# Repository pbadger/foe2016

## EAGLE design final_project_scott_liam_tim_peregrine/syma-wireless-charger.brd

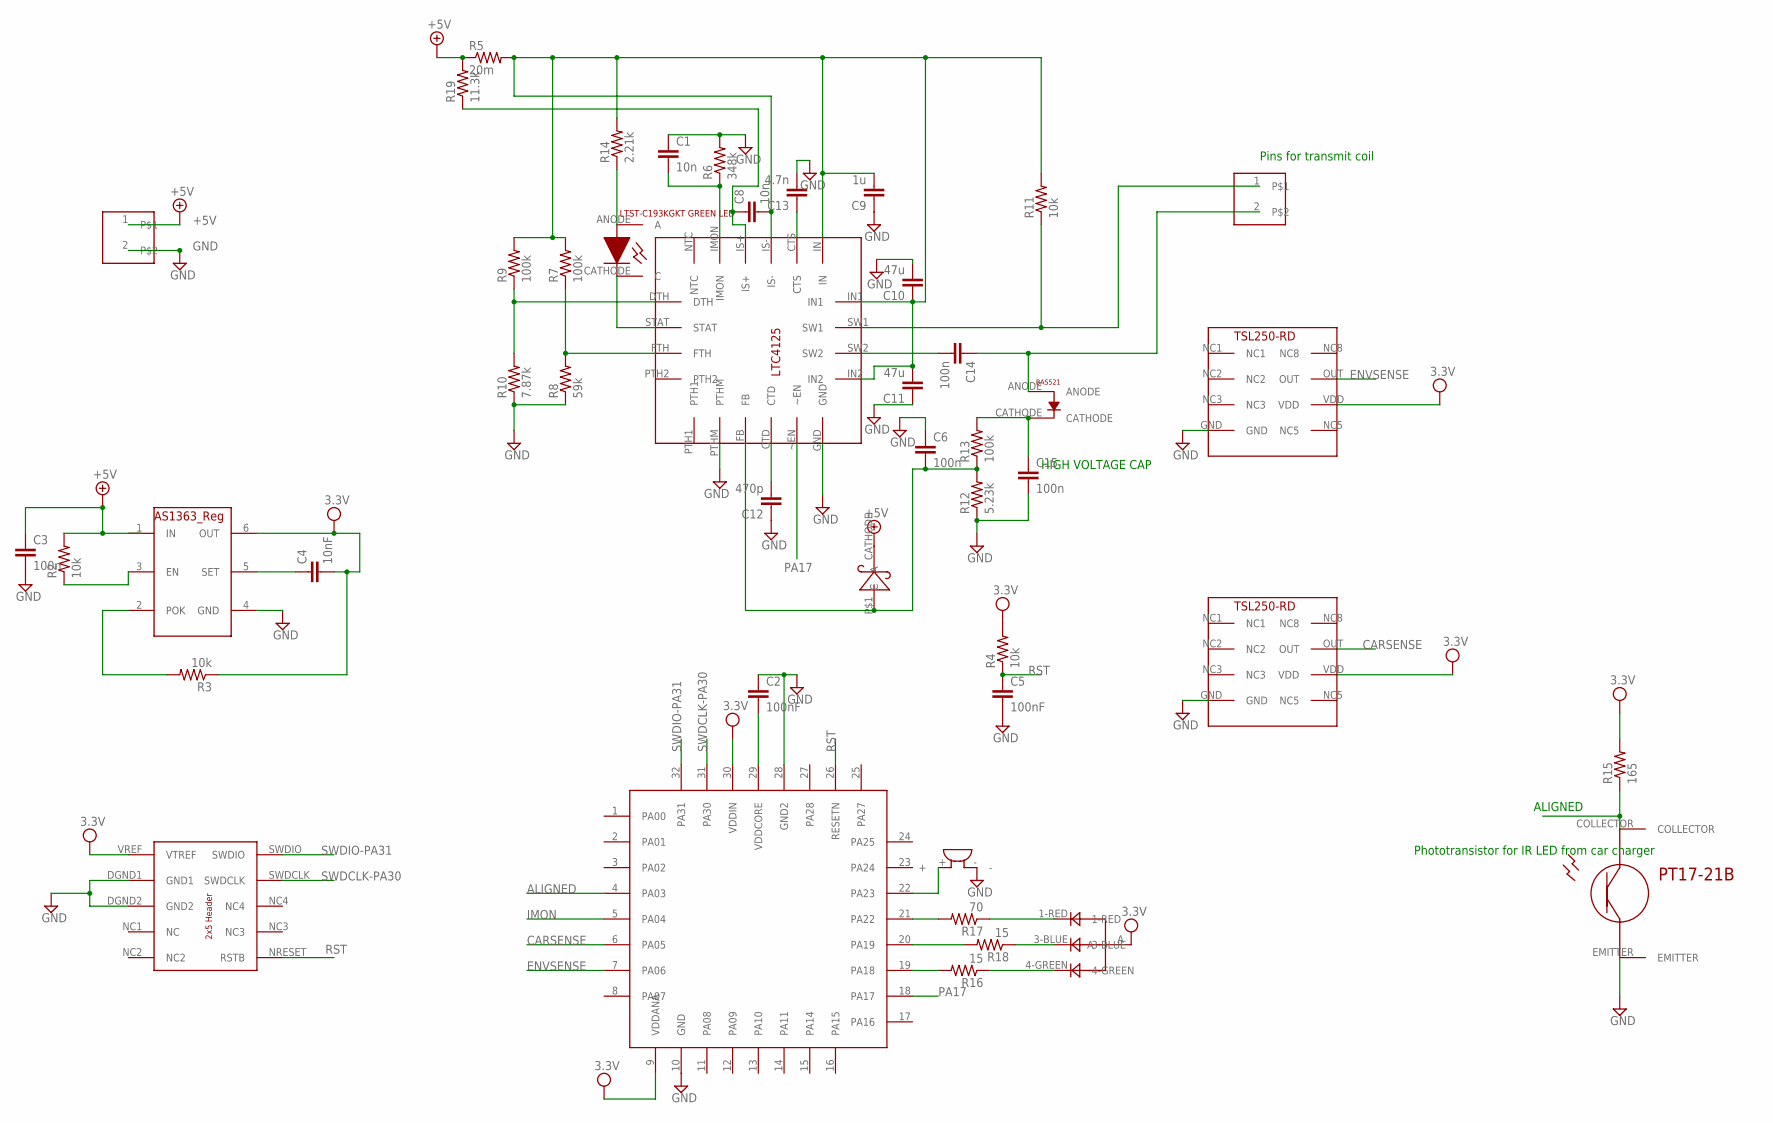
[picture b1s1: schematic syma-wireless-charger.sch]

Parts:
C1, C8: 10n; C0805
C2, C5: 100nF; C0805K
C3: 100n; C0805K
C4: 10nF; C0805K
C6: 100n; C0805
C9: 1u; C0805
C10, C11: 47u; C0805
C12: 470p; C0805
C13: 4.7n; C0805
C14: 100n; C1206
C15: 100n; C0603
DBG1: DEBUGHEAD
R2, R3, R4, R11: 10k; R0805
R5: 20m; R0805
R6: 348k; R0805
R7, R9, R13: 100k; R0805
R8: 59k; R0805
R10: 7.87k; R0805
R12: 5.23k; R0805
R14: 2.21k; R0805
R15: 165; R0805
R16, R18: 15; R0805
R17: 70; R0805
R19: 11.3k; R0805
U1: SAMD21E; TQFP32-08
U2: 3.3V_AS1363; SOT23-6
U$1: LTC4125; LTC1945-QFN
U$2: BAS521; BAS521-V-DIODE
U$3, U$11: 1X02
U$4: RGBLED
U$5: BUZZER
U$6, U$7: TSL250-RD
U$8: SCHTKYDIODE-523; SOD-523
U$9: LTST-C193KGKT_GREEN-LED
U$10: PT17-21B_PHOTOTRANSISTOR

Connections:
+5V: C3.1, R2.2, R5.1, R19.2, U2.1 (IN), U$3.1, U$8.CATHODE (C)
ALIGNED: R15.1, U1.4 (PA03), U$10.COLLECTOR
CARSENSE: U1.6 (PA05), U$6.OUT
ENVSENSE: U1.7 (PA06), U$7.OUT
GND: C1.1, C2.1, C3.2, C5.2, C6.1, C9.1, C10.2, C11.1, C12.1, C13.2, C15.2, DBG1.DGND1 (GND1), DBG1.DGND2 (GND2), R6.2, R8.1, R10.1, R12.1, U1.10 (GND), U1.28 (GND2), U2.4 (GND), U$1.GND, U$1.GND2, U$1.PTHM, U$3.2, U$5.-, U$6.GND, U$7.GND, U$10.EMITTER
IMON: U1.5 (PA04)
unnamed: C2.2, U1.29 (VDDCORE)
unnamed: R3.2, U2.2 (POK)
unnamed: R2.1, U2.3 (EN)
unnamed: R9.1, R10.2, U$1.DTH
unnamed: C4.1, U2.5 (SET)
unnamed: R7.1, R8.2, U$1.FTH
unnamed: R11.1, U$1.SW1, U$11.1
unnamed: C1.2, R6.1, U$1.IMON
unnamed: C6.2, R12.2, R13.1, U$1.FB, U$8.P$1 (A)
unnamed: C15.1, R13.2, U$2.CATHODE
unnamed: R14.1, U$9.ANODE (A)
unnamed: C14.1, U$2.ANODE, U$11.2
unnamed: R17.2, U1.21 (PA22)
unnamed: R18.2, U1.20 (PA19)
unnamed: R16.2, U1.19 (PA18)
unnamed: R16.1, U$4.4-GREEN
unnamed: R18.1, U$4.3-BLUE
unnamed: R17.1, U$4.1-RED
unnamed: U1.22 (PA23), U$5.+
unnamed: C8.2, C9.2, C10.1, C11.2, R5.2, R7.2, R9.2, R11.2, R14.2, U$1.IN, U$1.IN1, U$1.IN2, U$1.IS-
unnamed: C8.1, R19.1, U$1.IS+
unnamed: C14.2, U$1.SW2
unnamed: U$1.STAT, U$9.CATHODE (C)
unnamed: C12.2, U$1.CTD
unnamed: C13.1, U$1.CTS
PA17: U1.18 (PA17), U$1.~EN
RST: C5.1, DBG1.NRESET (RSTB), R4.1, U1.26 (RESETN)
SWDCLK-PA30: DBG1.SWDCLK, U1.31 (PA30)
SWDIO-PA31: DBG1.SWDIO, U1.32 (PA31)

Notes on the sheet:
Phototransistor for IR LED from car charger
Pins for transmit coil
HIGH VOLTAGE CAP
ALIGNED

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
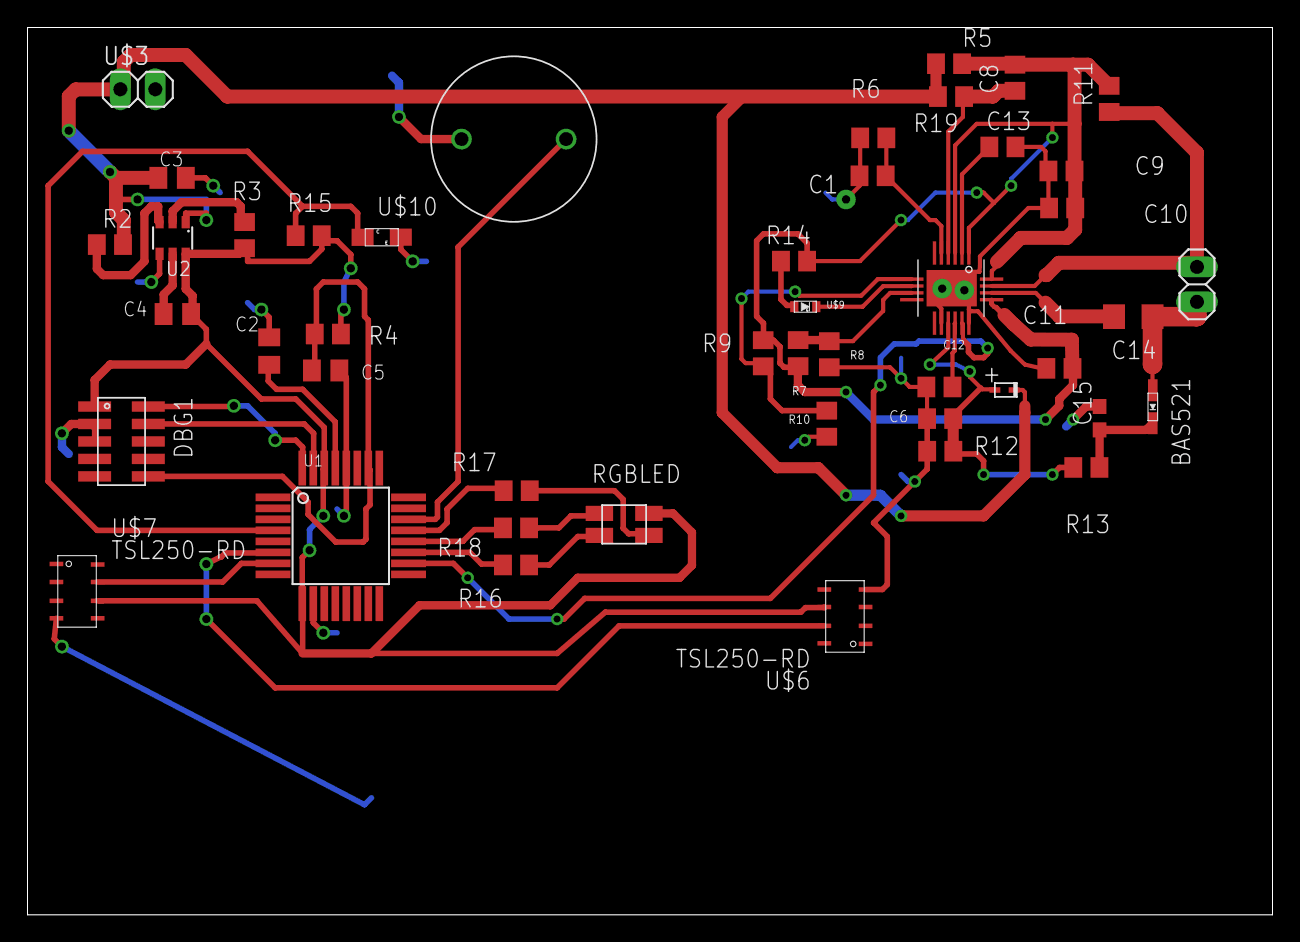
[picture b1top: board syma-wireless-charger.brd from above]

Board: 2 copper layers, 90.5 x 64.5 mm, 46 parts (0 on the bottom side), 35 nets.

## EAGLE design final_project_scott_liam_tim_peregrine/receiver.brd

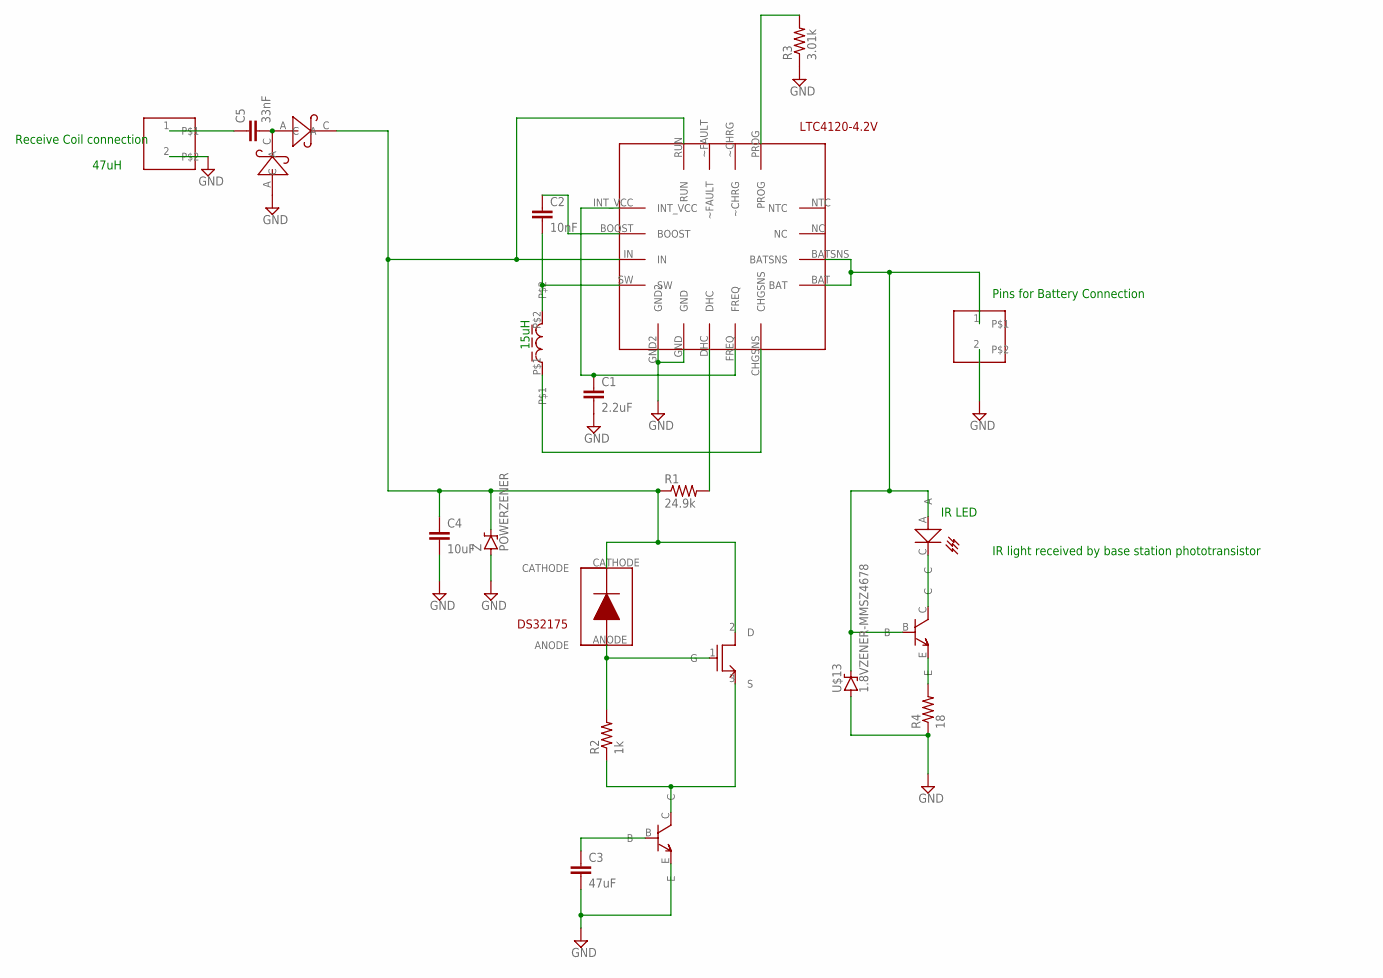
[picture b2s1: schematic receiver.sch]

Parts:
C1: 2.2uF; C0805K
C2: 10nF; C0805K
C3: 47uF; C0805K
C4: 10uF; C0805K
C5: 33nF; C0805K
PS, PS2: SCHTKYPOWER; POWERDI123
R1: 24.9k; R0805
R2: 1k; R0805
R3: 3.01k; R0805
R4: 18; R0805
U$1: LTC4120-4.2V
U$2, U$10: 1X02
U$3: 15UH-INDUCTOR
U$4: BAS521; BAS521-V-DIODE
U$5: M1-RSD140P06; DPAKTO252
U$6, U$14: NPN-MMBT3904; SOT23
U$11: IRLED
U$13: 1.8VZENER-MMSZ4678; SOD-123
Z: POWERZENER; POWERDI123

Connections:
GND: C1.2, C3.2, C4.2, PS2.A, R3.1, R4.1, U$1.GND, U$1.GND2, U$2.2, U$6.E, U$10.2, U$13.A, Z.A
unnamed: C1.1, U$1.FREQ, U$1.INT_VCC
unnamed: U$1.CHGSNS, U$3.P$1
unnamed: C4.1, PS.C, R1.1, U$1.IN, U$1.RUN, U$4.CATHODE, U$5.2 (D), Z.C
unnamed: C2.1, U$1.BOOST
unnamed: C2.2, U$1.SW, U$3.P$2
unnamed: R1.2, U$1.DHC
unnamed: R2.2, U$4.ANODE, U$5.1 (G)
unnamed: R2.1, U$5.3 (S), U$6.C
unnamed: C5.1, U$2.1
unnamed: C5.2, PS.A, PS2.C
unnamed: C3.1, U$6.B
unnamed: R3.2, U$1.PROG
unnamed: U$1.BAT, U$1.BATSNS, U$10.1, U$11.A, U$13.C, U$14.B
unnamed: R4.2, U$14.E
unnamed: U$11.C, U$14.C

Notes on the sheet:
15uH
Pins for Battery Connection
IR LED
IR light received by base station phototransistor
Receive Coil connection
47uH

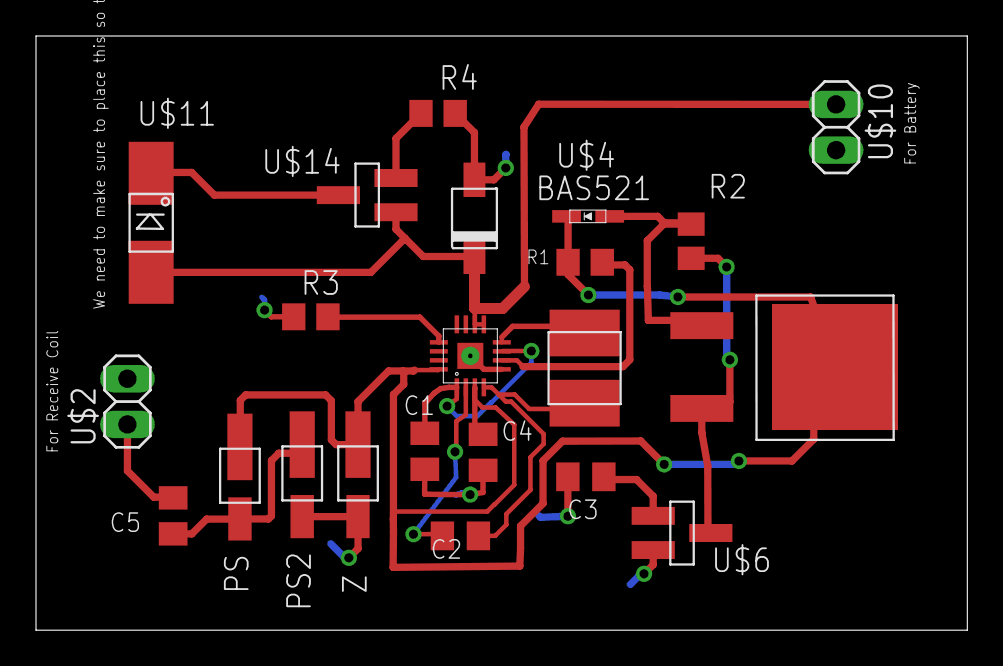
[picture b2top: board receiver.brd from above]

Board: 2 copper layers, 51.7 x 33.0 mm, 22 parts (0 on the bottom side), 16 nets.

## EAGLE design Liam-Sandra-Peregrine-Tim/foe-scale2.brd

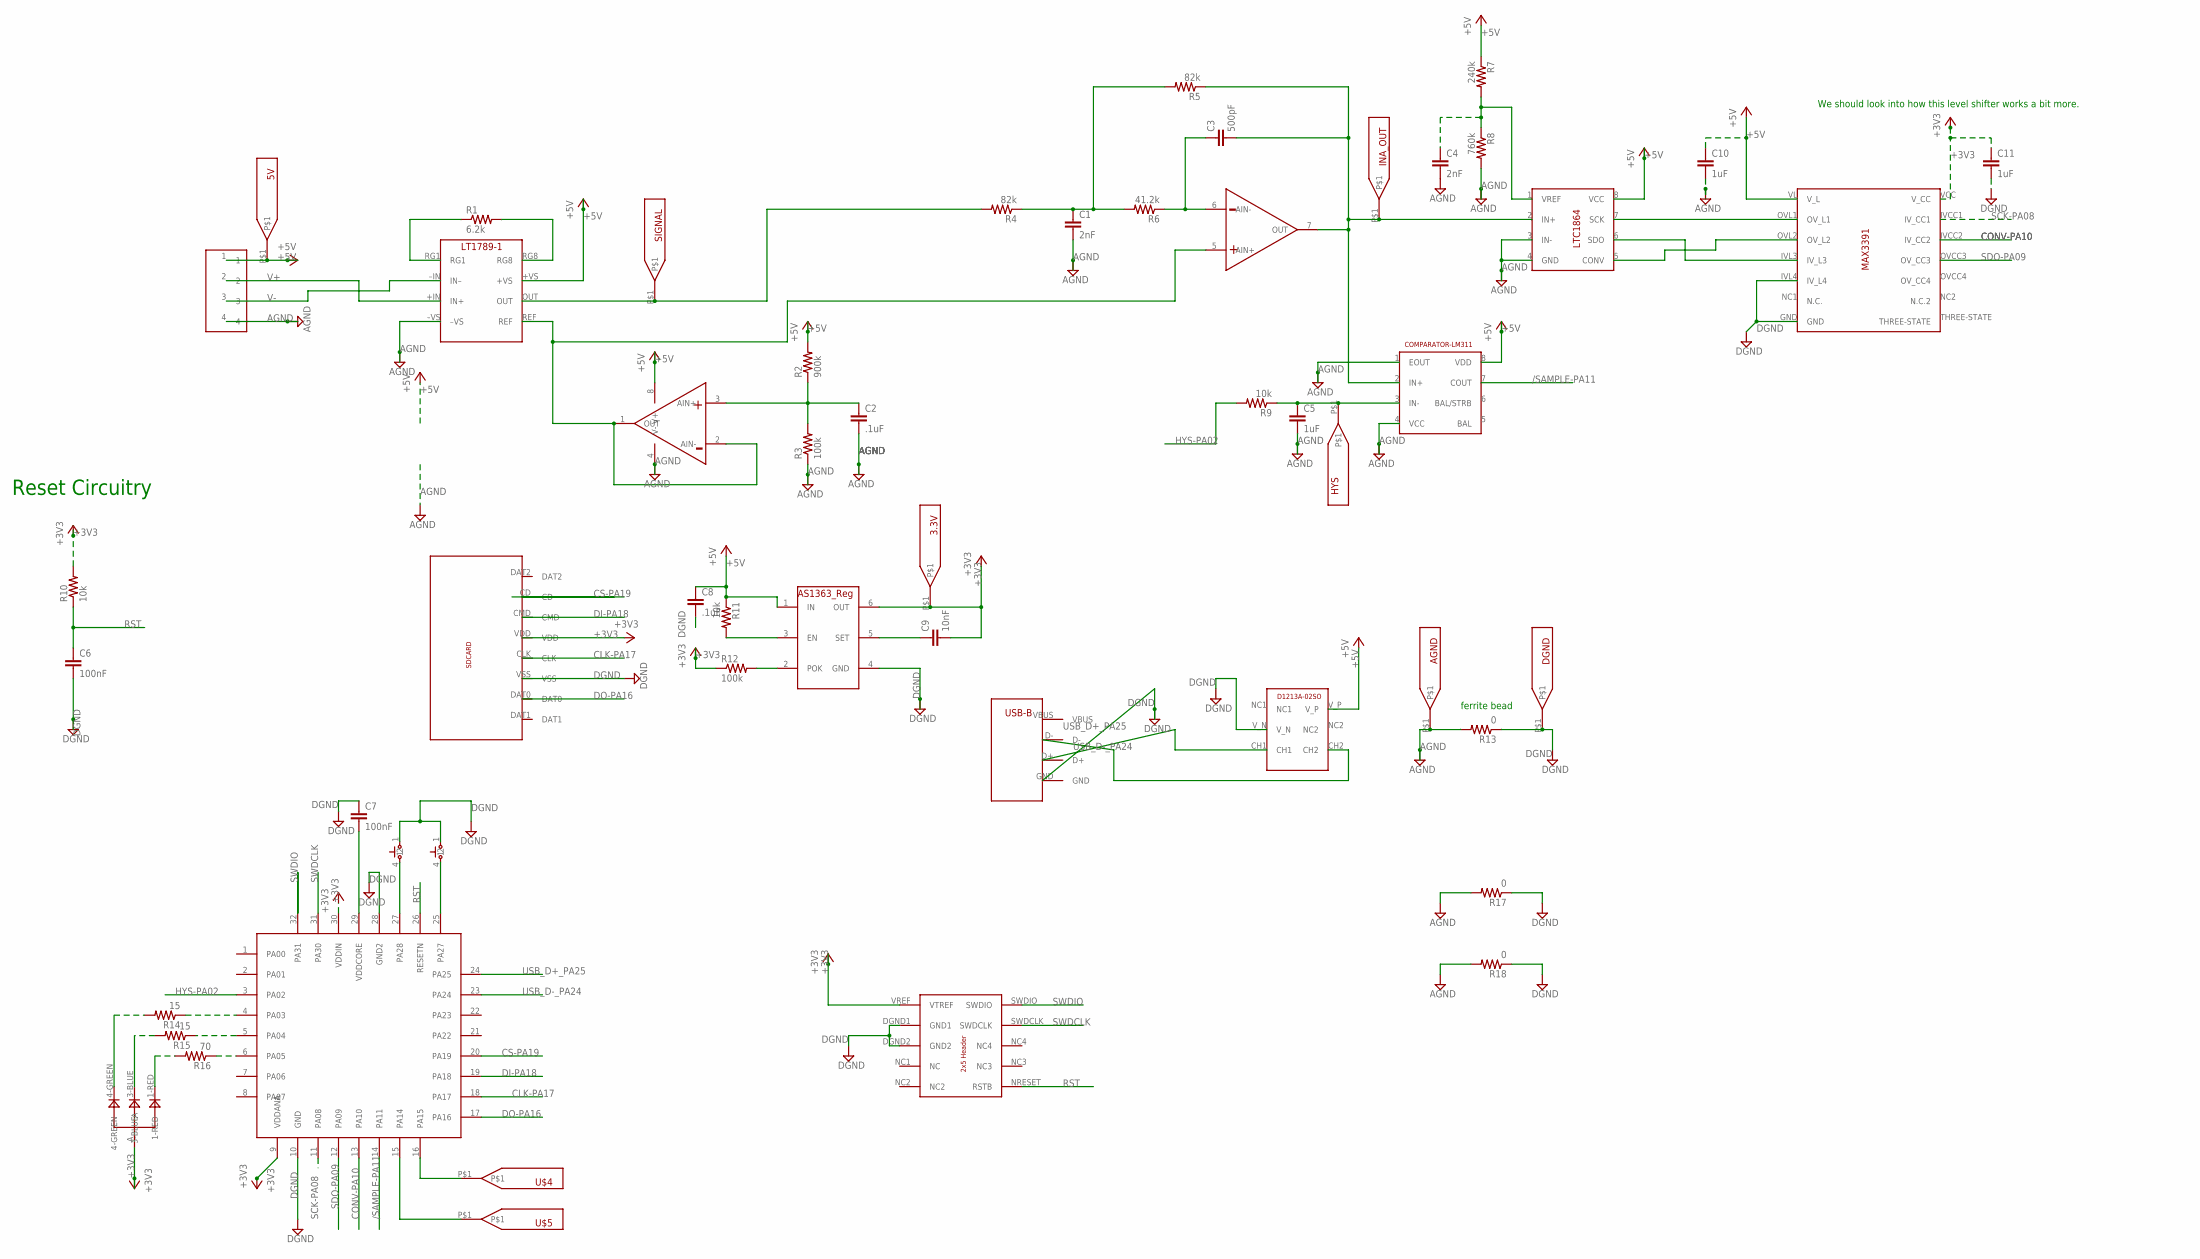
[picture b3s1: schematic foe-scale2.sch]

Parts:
3.3V, 5V: TEST_POINT
AGND: TEST_POINT
AS1363: 3.3V_AS1363; SOT23-6
C1, C4: 2nF; C0805K
C2, C8: .1uF; C0805K
C3: 500pF; C0805K
C5, C10, C11: 1uF; C0805K
C6, C7: 100nF; C0805K
C9: 10nF; C0805K
D1: D1213A-DIODE-ARRAY; SOT26-DIODE-ARRAY
DBG1: DEBUGHEAD
DGND: TEST_POINT
HYS: TEST_POINT
INA_OUT: TEST_POINT
R1: 6.2k; R0805
R2: 900k; R0805
R3, R12: 100k; R0805
R4, R5: 82k; R0805
R6: 41.2k; R0805
R7: 240k; R0805
R8: 760k; R0805
R9, R10, R11: 10k; R0805
R13, R17, R18: 0; R0805
R14, R15: 15; R0805
R16: 70; R0805
SIGNAL: TEST_POINT
U1: LM311; SOIC8
U2: SAMD21E; TQFP32-08
U$1: 1X04
U$2: LT1789-1-INSTR-AMP; S8-LT1789-1
U$3: LMC6482; SOIC8
U$4, U$5: TEST_POINT
U$6: ADC-LTC1864; SOIC8
U$7: LEVEL-SHIFTER; TSSOP-14
U$8: SDCARD_JACK; MICRO_SDCARD
U$10: RGBLED
U$11, U$12: BUTTON_THRU; PUSHBTN
U$13: USB-B

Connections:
+3V3: 3.3V.P$1, AS1363.6 (OUT), C9.2, C11.1, DBG1.VREF (VTREF), R10.2, R12.1, U2.9 (VDDANA), U2.30 (VDDIN), U$7.VCC (V_CC), U$8.VDD, U$10.A
+5V: 5V.P$1, AS1363.1 (IN), C8.1, C10.1, D1.V_P, R2.2, R7.1, R11.1, U1.8 (VDD), U$1.1, U$2.+VS, U$3.8 (V+), U$6.8 (VCC), U$7.VL (V_L)
/SAMPLE-PA11: U1.7 (COUT), U2.14 (PA11)
AGND: AGND.P$1, C1.2, C2.2, C4.2, C5.2, C10.2, R3.1, R8.2, R13.2, R17.2, R18.2, U1.1 (EOUT), U1.4 (VCC), U$1.4, U$2.–VS, U$3.4 (V-), U$6.3 (IN-), U$6.4 (GND)
CLK-PA17: U2.18 (PA17), U$8.CLK
CONV-PA10: U2.13 (PA10), U$7.IVCC2 (IV_CC2)
CS-PA19: U2.20 (PA19), U$8.CD
DBG-2-PA16: U2.16 (PA15), U$4.P$1
DBG-PIN-PA14: U2.15 (PA14), U$5.P$1
DGND: AS1363.4 (GND), C6.2, C7.1, C8.2, C11.2, D1.V_N, DBG1.DGND1 (GND1), DBG1.DGND2 (GND2), DGND.P$1, R13.1, R17.1, R18.1, U2.10 (GND), U2.28 (GND2), U$7.GND, U$7.IVL4 (IV_L4), U$8.VSS, U$11.1, U$12.1, U$13.GND
DI-PA18: U2.19 (PA18), U$8.CMD
DO-PA16: U2.17 (PA16), U$8.DAT0
HYS-PA02: R9.2, U2.3 (PA02)
unnamed: R14.1, U2.4 (PA03)
unnamed: U2.27 (PA28), U$12.4 (2)
unnamed: U2.25 (PA27), U$11.4 (2)
unnamed: R15.1, U2.5 (PA04)
unnamed: R1.1, U$2.RG1
unnamed: R1.2, U$2.RG8
unnamed: R4.2, SIGNAL.P$1, U$2.OUT
unnamed: R16.1, U2.6 (PA05)
unnamed: C2.1, R2.1, R3.2, U$3.3 (AIN+)
unnamed: U$2.REF, U$3.1 (OUT), U$3.2 (AIN-), U$3.5 (AIN+)
unnamed: C1.1, R4.1, R5.2, R6.2
unnamed: C3.2, INA_OUT.P$1, R5.1, U1.2 (IN+), U$3.7 (OUT), U$6.2 (IN+)
unnamed: C3.1, R6.1, U$3.6 (AIN-)
unnamed: C4.1, R7.2, R8.1, U$6.1 (VREF)
unnamed: C5.1, HYS.P$1, R9.1, U1.3 (IN-)
unnamed: U$6.7 (SCK), U$7.OVL1 (OV_L1)
unnamed: U$6.5 (CONV), U$7.OVL2 (OV_L2)
unnamed: U$6.6 (SDO), U$7.IVL3 (IV_L3)
unnamed: C7.2, U2.29 (VDDCORE)
unnamed: R14.2, U$10.4-GREEN
unnamed: R15.2, U$10.3-BLUE
unnamed: R16.2, U$10.1-RED
unnamed: AS1363.3 (EN), R11.2
unnamed: AS1363.5 (SET), C9.1
unnamed: AS1363.2 (POK), R12.2
RST: C6.1, DBG1.NRESET (RSTB), R10.1, U2.26 (RESETN)
SCK-PA08: U2.11 (PA08), U$7.IVCC1 (IV_CC1)
SDO-PA09: U2.12 (PA09), U$7.OVCC3 (OV_CC3)
SWDCLK: DBG1.SWDCLK, U2.31 (PA30)
SWDIO: DBG1.SWDIO, U2.32 (PA31)
USB_D+_PA25: D1.CH1, U2.24 (PA25), U$13.D+
USB_D-_PA24: D1.CH2, U2.23 (PA24), U$13.D-
V+: U$1.2, U$2.+IN (IN+)
V-: U$1.3, U$2.–IN (IN–)

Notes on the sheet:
We should look into how this level shifter works a bit more.
Reset Circuitry
ferrite bead

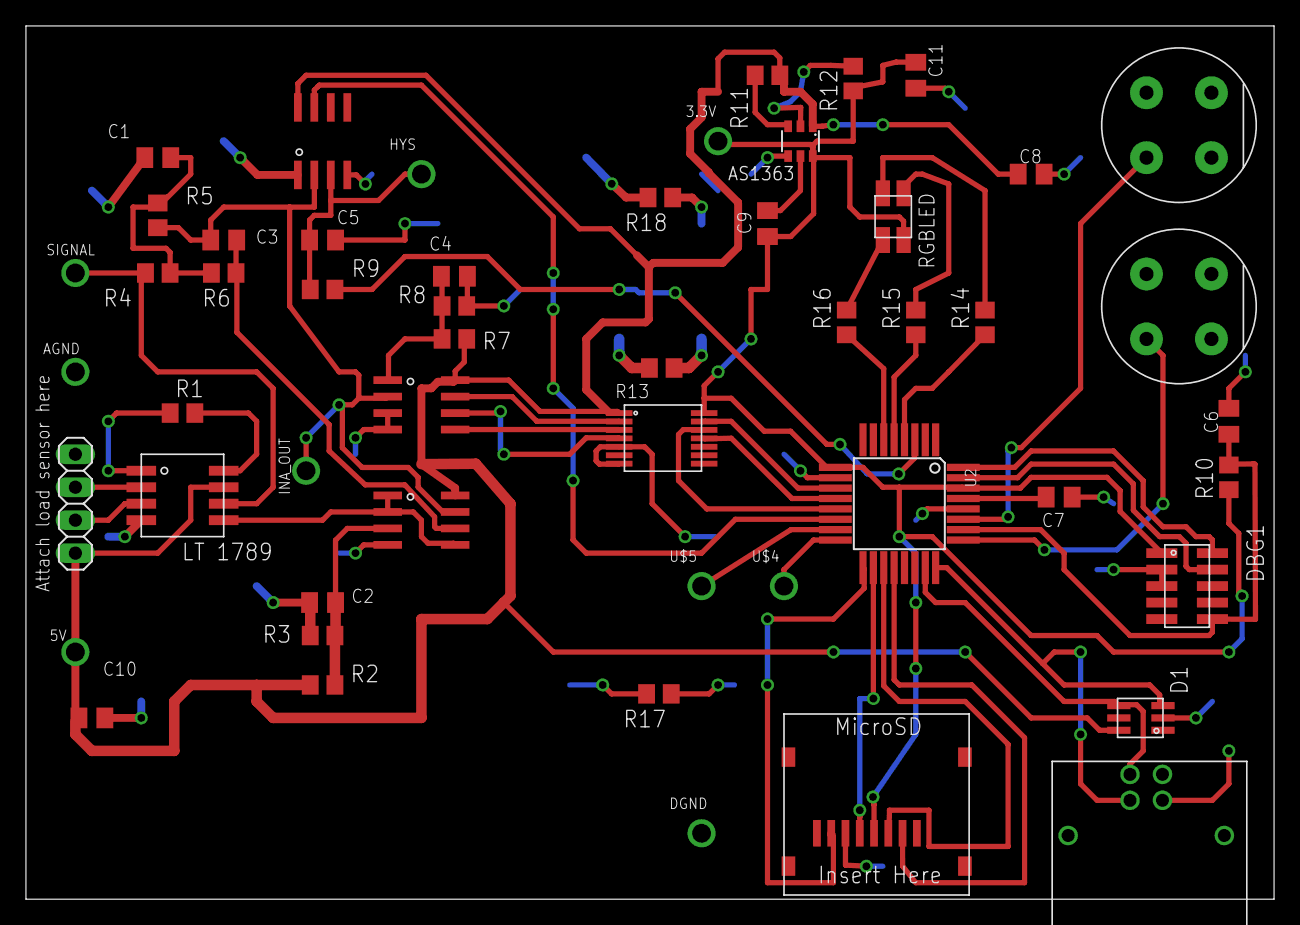
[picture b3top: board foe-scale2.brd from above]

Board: 2 copper layers, 96.2 x 67.3 mm, 53 parts (0 on the bottom side), 47 nets.

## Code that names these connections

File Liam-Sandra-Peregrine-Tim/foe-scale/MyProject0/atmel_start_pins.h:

/*
 * Code generated from Atmel Start.
 *
 * This file will be overwritten when reconfiguring your Atmel Start project.
 * Please copy examples or other code you want to keep to a separate file
 * to avoid losing it when reconfiguring.
 */
#ifndef ATMEL_START_PINS_H_INCLUDED
#define ATMEL_START_PINS_H_INCLUDED

#include <hal_gpio.h>

#define PA00  GPIO(GPIO_PORTA, 0)
#define PA01  GPIO(GPIO_PORTA, 1)
#define PA03  GPIO(GPIO_PORTA, 3)
#define PA04  GPIO(GPIO_PORTA, 4)
#define PA05  GPIO(GPIO_PORTA, 5)
#define PA06  GPIO(GPIO_PORTA, 6)
#define PA24  GPIO(GPIO_PORTA, 24)
#define PA25  GPIO(GPIO_PORTA, 25)

// Level shifter
#define SCK  GPIO(GPIO_PORTA, 8)
#define SDI  GPIO(GPIO_PORTA, 22)
#define CONV  GPIO(GPIO_PORTA, 10)


#endif // ATMEL_START_PINS_H_INCLUDED

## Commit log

2016-04-05 added schematic
2016-04-05 replaced library with updated one
2016-04-06 got most of the parts for the schematic in
2016-04-06 added the layout file
2016-04-06 finished up schematic
2016-04-06 updated layout file
2016-04-06 added some labels, consolidated space, moved some parts around to generate dividing plane
2016-04-08 minor changes
2016-04-08 added power and gnd connections
2016-04-09 made a few changes to layout
2016-04-09 finished up layout. Try to place all of the names and values of th components so that they do not overlap. To do so, use the smash command by typing smash and then clicking on the component. Xs will 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
2016-04-11 committing in addition to saving because fck Eagle
2016-04-11 eagle why you gotta be that way?
2016-04-12 DRC check done, one more connection of grounds, and 2 DBG pins on MCU
2016-04-13 fixed up a couple things in board
2016-04-13 pushing
2016-04-13 replaced microUSB with standard USB B
2016-04-24 final project setup
2016-04-25 added three parts to the library
2016-04-26 added more packages to the library
2016-04-26 added NPN transistor
2016-04-26 added a few more parts to the library
2016-04-27 adding components
2016-04-27 almost completed components
2016-04-27 added diodes
2016-04-28 created file for schematic
2016-04-29 worked on the schematic a bit
2016-04-29 completed receiver schematic, increased the footprint size of some devices in our library and added a bit more to the transmitter schematic
2016-04-29 started tranmitter circuit
2016-04-29 finished uC
2016-04-29 Error checked receiver
2016-04-29 Added to Schematic
2016-04-30 removed lock, added light sensors and couple connections to 4125
2016-04-30 more 4125 updates
2016-04-30 added receiver board
2016-04-30 fixed green LED symbol
2016-04-30 started transmitter layout
2016-05-01 Fixed some packages
2016-05-01 lock issues fixed
2016-05-01 Started Transceiver Layout
2016-05-02 lock update
2016-05-03 added code
2016-05-03 checking if my virtual machine is linked to git
2016-05-03 placed parts for transmitter board. no traces yet
2016-05-03 mostly finished traces
2016-05-03 moved the light detectors to be farther from each other
2016-05-03 Fixed errors
2016-05-03 drc checking on receiver
2016-05-03 fixed up some overlap stuff on the transmitter
2016-05-03 fixed errors, added aesthetic silkscreen
2016-05-03 Fixed ambient light sensor
2016-05-03 minor error checking
2016-05-05 got ADC to work
2016-05-06 updated code. Changed serial data pin to PA22
2016-05-10 added a few features to atmel_start file
